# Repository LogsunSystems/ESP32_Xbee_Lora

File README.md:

# Introduction
This is ESP-32 based Wireless Interfacing board which supports Zigbee or LoRa. The board  comes with
either Zigbee or LoRa not both  at a time.

## On-Board Peripherals
The board has sevral On-Board Peripherals like 
	1. LED Bar Graph

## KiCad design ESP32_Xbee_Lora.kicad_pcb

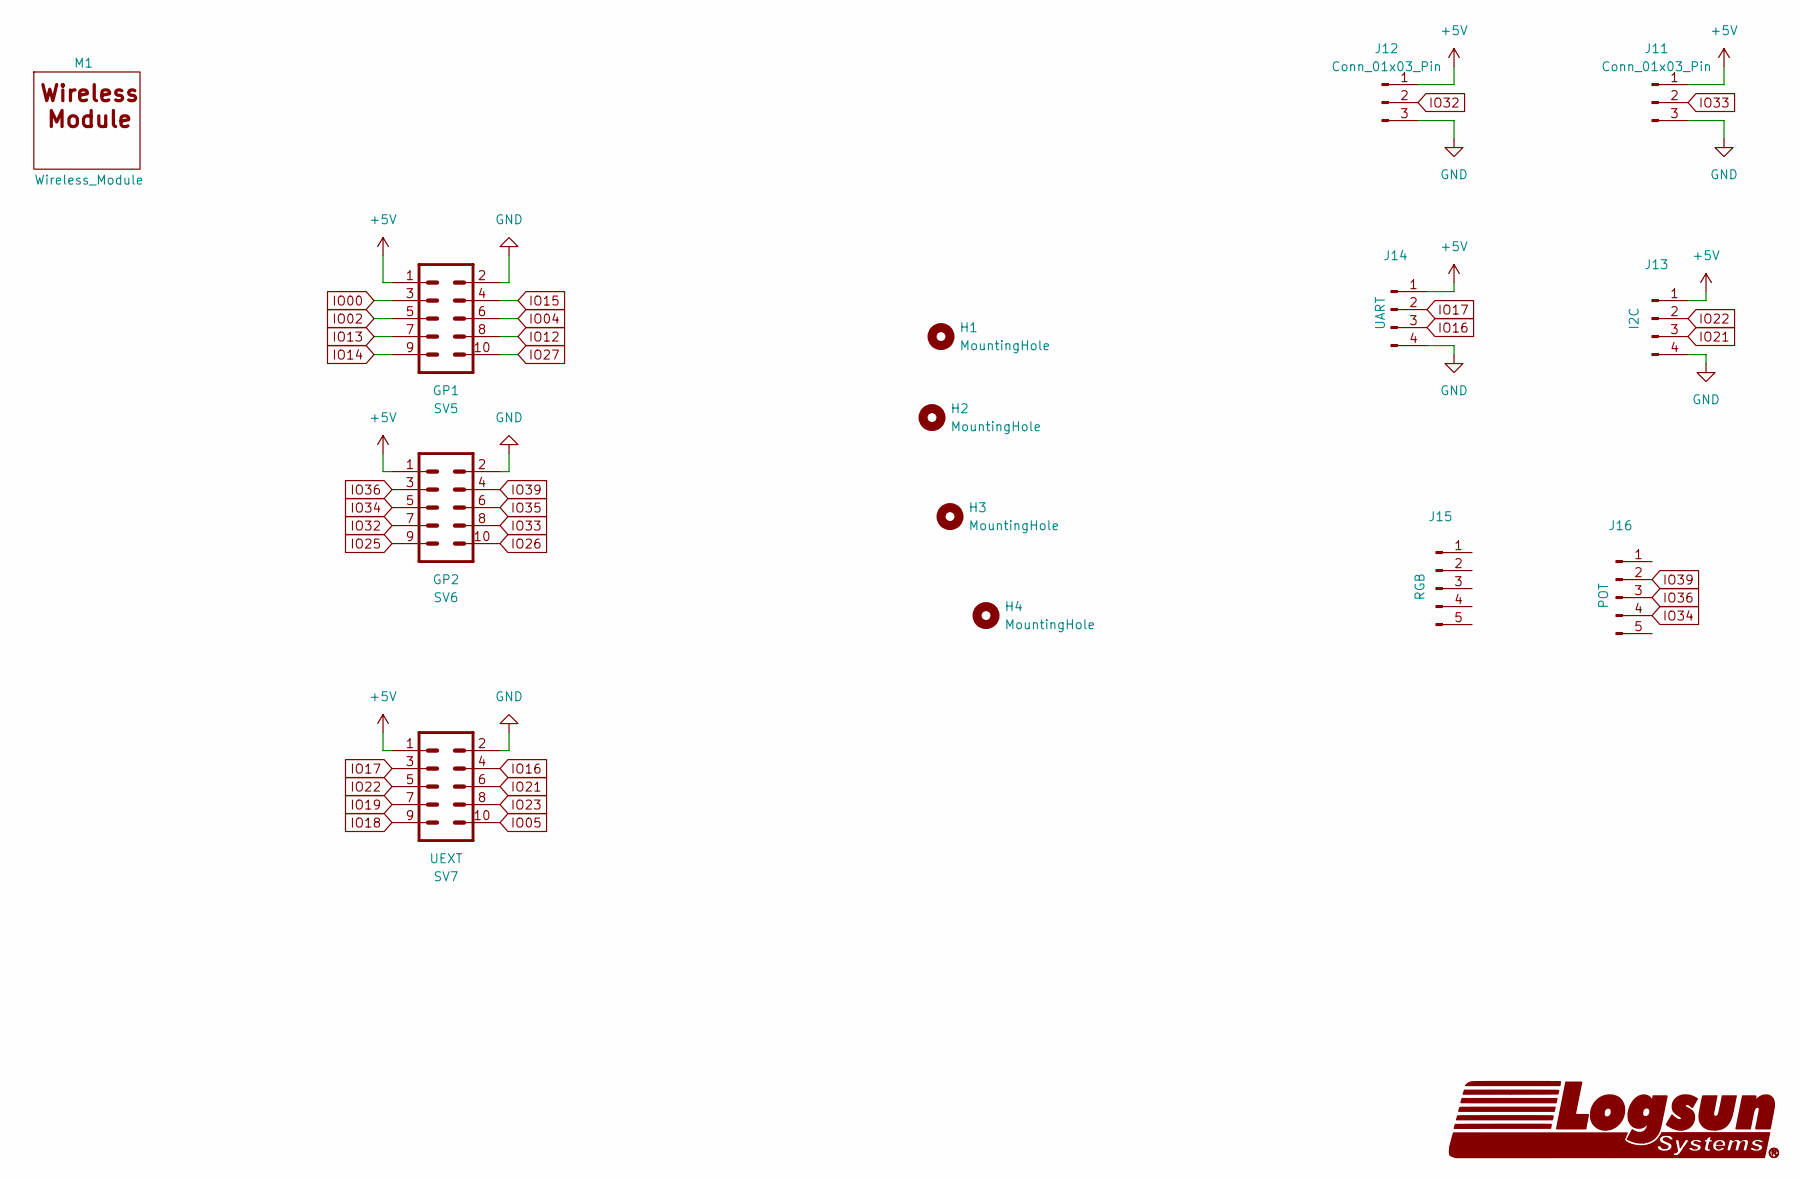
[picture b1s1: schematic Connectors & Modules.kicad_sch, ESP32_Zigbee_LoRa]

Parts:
H1, H2, H3, H4: MountingHole; MountingHole_3.2mm_M3_Pad_Via
J11, J12: Conn_01x03_Pin; JST_EH_B3B-EH-A_1x03_P2.50mm_Vertical
J13: I2C; JST_EH_B4B-EH-A_1x04_P2.50mm_Vertical
J14: UART; JST_EH_B4B-EH-A_1x04_P2.50mm_Vertical
J15: RGB; JST_EH_B5B-EH-A_1x05_P2.50mm_Vertical
J16: POT; JST_EH_B5B-EH-A_1x05_P2.50mm_Vertical
M1: Wireless_Module; LGS-KC-Wireless_Mod
SV5: GP1; LGS-KC-ML10-CONTROLLER
SV6: GP2; LGS-KC-ML10-CONTROLLER
SV7: UEXT; LGS-KC-ML10-CONTROLLER

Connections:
+5V: J11.1, J12.1, J13.1, J14.1, SV5.1, SV6.1, SV7.1; also elsewhere on the board
GND: J11.3, J12.3, J13.4, J14.4, SV5.2, SV6.2, SV7.2; also elsewhere on the board
IO00: SV5.3; also elsewhere on the board
IO02: SV5.5; also elsewhere on the board
IO04: SV5.6; also elsewhere on the board
IO05: SV7.10; also elsewhere on the board
IO12: SV5.8; also elsewhere on the board
IO13: SV5.7; also elsewhere on the board
IO14: SV5.9; also elsewhere on the board
IO15: SV5.4; also elsewhere on the board
IO16: J14.3, SV7.4; also elsewhere on the board
IO17: J14.2, SV7.3; also elsewhere on the board
IO18: SV7.9; also elsewhere on the board
IO19: SV7.7; also elsewhere on the board
IO21: J13.3, SV7.6; also elsewhere on the board
IO22: J13.2, SV7.5; also elsewhere on the board
IO23: SV7.8; also elsewhere on the board
IO25: SV6.9; also elsewhere on the board
IO26: SV6.10; also elsewhere on the board
IO27: SV5.10; also elsewhere on the board
IO32: J12.2, SV6.7; also elsewhere on the board
IO33: J11.2, SV6.8; also elsewhere on the board
IO34: J16.4, SV6.5; also elsewhere on the board
IO35: SV6.6; also elsewhere on the board
IO36: J16.3, SV6.3; also elsewhere on the board
IO39: J16.2, SV6.4; also elsewhere on the board

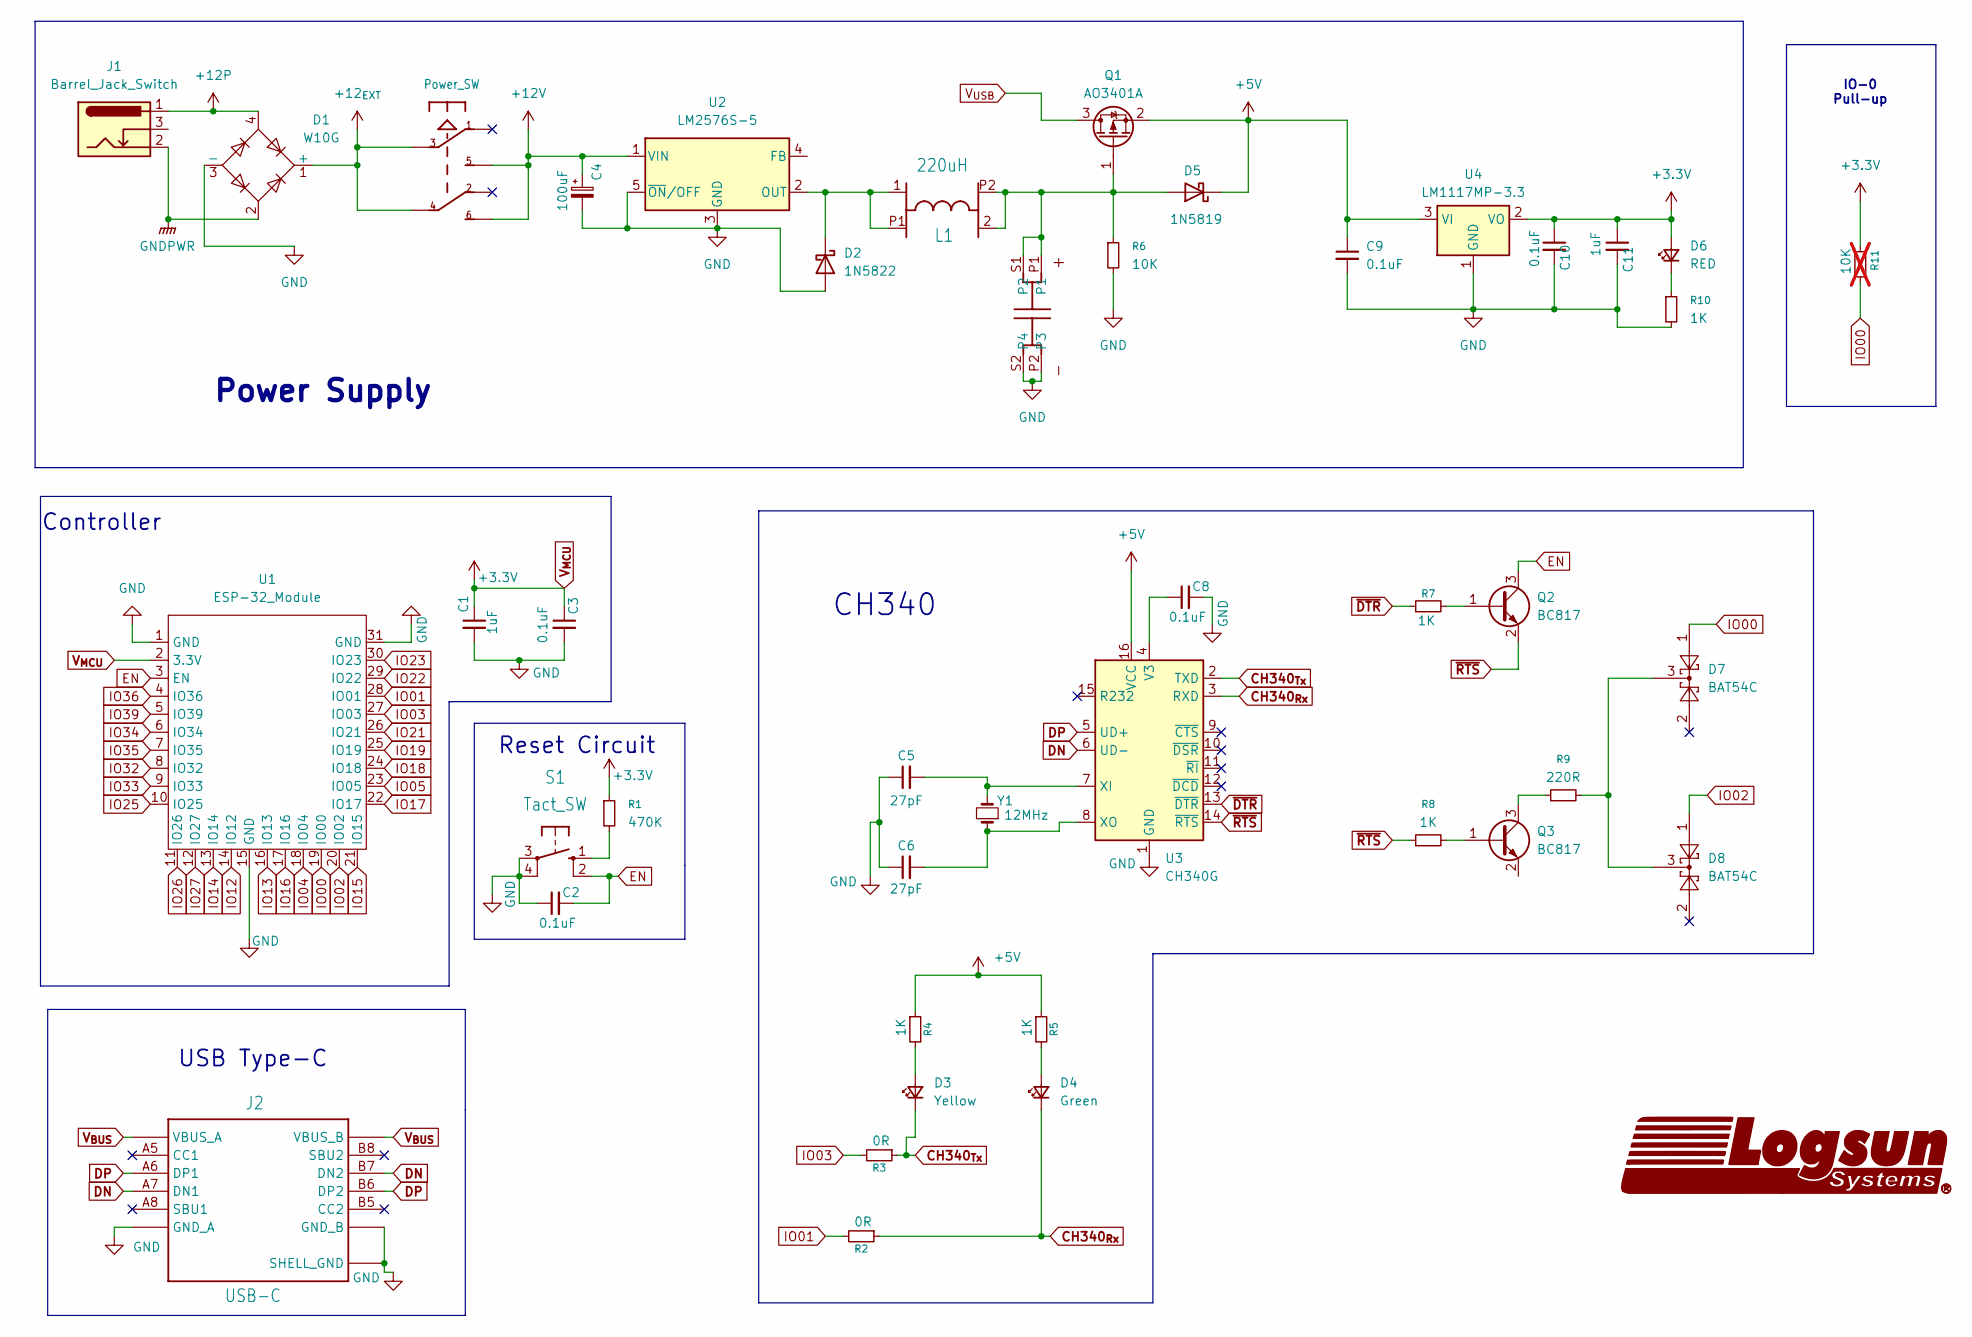
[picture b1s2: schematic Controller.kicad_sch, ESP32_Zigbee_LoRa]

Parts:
C1, C11: 1uF; C_0805_2012Metric_Pad1.18x1.45mm_HandSolder
C2, C3, C8, C9, C10: 0.1uF; C_0805_2012Metric_Pad1.18x1.45mm_HandSolder
C4: 100uF; C_0805_2012Metric_Pad1.18x1.45mm_HandSolder
C5, C6: 27pF; C_0805_2012Metric_Pad1.18x1.45mm_HandSolder
C7: 1000uF; LGS-KC-140CLH-1010
D1: W10G; Diode_Bridge_Round_D9.8mm
D2: 1N5822; D_DO-201AD_P15.24mm_Horizontal
D3: Yellow; LED_1206_3216Metric_ReverseMount_Hole1.8x2.4mm
D4: Green; LED_1206_3216Metric_ReverseMount_Hole1.8x2.4mm
D5: 1N5819; D_DO-41_SOD81_P10.16mm_Horizontal
D6: RED; LED_1206_3216Metric_ReverseMount_Hole1.8x2.4mm
D7, D8: BAT54C; SOT-23
J1: Barrel_Jack_Switch; BarrelJack_Horizontal
J2: USB-C; LGS-KC-VALCON_CSP-USC16-TR
L1: 220uH; LGS-KC-MS42
Q1: AO3401A; SOT-23
Q2, Q3: BC817; SOT-23
R1: 470K; R_0805_2012Metric_Pad1.20x1.40mm_HandSolder
R2, R3: 0R; R_0805_2012Metric_Pad1.20x1.40mm_HandSolder
R4, R5, R7, R8, R10: 1K; R_0805_2012Metric_Pad1.20x1.40mm_HandSolder
R6: 10K; R_0805_2012Metric_Pad1.20x1.40mm_HandSolder
R9: 220R; R_1206_3216Metric_Pad1.30x1.75mm_HandSolder
R11: 10K; R_0805_2012Metric_Pad1.20x1.40mm_HandSolder; not fitted
S1: Tact_SW; LGS-KC-B3F-10XX
SW1: Power_SW; LGS-KC-SLIDE
U1: ESP-32_Module; esp 32 wroom module
U2: LM2576S-5; TO-263-5_TabPin3
U3: CH340G; SOIC-16_3.9x9.9mm_P1.27mm
U4: LM1117MP-3.3; SOT-223-3_TabPin2
Y1: 12MHz; Crystal_HC49-4H_Vertical

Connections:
+5V: C9.1, D5.1 (K), Q1.2 (S), R4.1, R5.1, U3.16 (VCC), U4.3 (VI); also elsewhere on the board
+12P: D1.4, J1.1
+12V: C4.1, SW1.5, SW1.6, U2.1 (VIN)
+12_{EXT}: D1.1 (+), SW1.3, SW1.4
CH340_{Rx}: D4.1 (K), R2.1, U3.3 (RXD)
CH340_{Tx}: D3.1 (K), R3.1, U3.2 (TXD)
DN: J2.A7 (DN1), J2.B7 (DN2), U3.6 (UD-)
DP: J2.A6 (DP1), J2.B6 (DP2), U3.5 (UD+)
EN: C2.2, Q2.3 (C), S1.2 (S1), U1.3 (EN)
GND: C1.2, C2.1, C3.2, C4.2, C5.1, C6.1, C7.P2 (P3), C7.S2 (P4), C8.2, C9.2, C10.2, C11.2, D1.3 (-), D2.2 (A), J2.A1 (GND_A), J2.A12 (GND_A), J2.B1 (GND_B), J2.B12 (GND_B), J2.S1 (SHELL_GND), J2.S2 (SHELL_GND), J2.S3 (SHELL_GND), J2.S4 (SHELL_GND), R6.2, R10.2, S1.3, S1.4 (P1), U1.1 (GND), U1.15 (GND), U1.31 (GND), U2.3 (GND), U2.5 (~ON/OFF), U3.1 (GND), U4.1 (GND); also elsewhere on the board
GNDPWR: D1.2, J1.2
IO00: D7.1, R11.2, U1.19 (IO00); also elsewhere on the board
IO01: R2.2, U1.28 (IO01)
IO02: D8.1, U1.20 (IO02); also elsewhere on the board
IO03: R3.2, U1.27 (IO03)
IO04: U1.18 (IO04); also elsewhere on the board
IO05: U1.23 (IO05); also elsewhere on the board
IO12: U1.14 (IO12); also elsewhere on the board
IO13: U1.16 (IO13); also elsewhere on the board
IO14: U1.13 (IO14); also elsewhere on the board
IO15: U1.21 (IO15); also elsewhere on the board
IO16: U1.17 (IO16); also elsewhere on the board
IO17: U1.22 (IO17); also elsewhere on the board
IO18: U1.24 (IO18); also elsewhere on the board
IO19: U1.25 (IO19); also elsewhere on the board
IO21: U1.26 (IO21); also elsewhere on the board
IO22: U1.29 (IO22); also elsewhere on the board
IO23: U1.30 (IO23); also elsewhere on the board
IO25: U1.10 (IO25); also elsewhere on the board
IO26: U1.11 (IO26); also elsewhere on the board
IO27: U1.12 (IO27); also elsewhere on the board
IO32: U1.8 (IO32); also elsewhere on the board
IO33: U1.9 (IO33); also elsewhere on the board
IO34: U1.6 (IO34); also elsewhere on the board
IO35: U1.7 (IO35); also elsewhere on the board
IO36: U1.4 (IO36); also elsewhere on the board
IO39: U1.5 (IO39); also elsewhere on the board
unnamed: C7.P1, C7.S1 (P2), D5.2 (A), L1.2 (3), L1.P2 (4), Q1.1 (G), R6.1
unnamed: D2.1 (K), L1.1, L1.P1 (2), U2.2 (OUT)
unnamed: D3.2 (A), R4.2
unnamed: D4.2 (A), R5.2
unnamed: D6.1 (K), R10.1
unnamed: D7.3, D8.3, R9.2
unnamed: Q2.1 (B), R7.2
unnamed: Q3.1 (B), R8.2
unnamed: Q3.3 (C), R9.1
unnamed: R1.2, S1.1 (S)
unnamed: C8.1, U3.4 (V3)
unnamed: C5.2, U3.7 (XI), Y1.2
unnamed: C6.2, U3.8 (XO), Y1.1
V_{BUS}: J2.A4 (VBUS_A), J2.A9 (VBUS_A), J2.B4 (VBUS_B), J2.B9 (VBUS_B)
V_{MCU}: C1.1, C3.1, C10.1, C11.1, D6.2 (A), R1.1, R11.1, U1.2 (3.3V), U4.2 (VO)
V_{USB}: Q1.3 (D)
~DTR: R7.1, U3.13 (~DTR)
~RTS: Q2.2 (E), R8.1, U3.14 (~RTS)

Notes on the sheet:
Reset Circuit
Power Supply
Controller
IO-0 Pull-up
USB Type-C
CH340

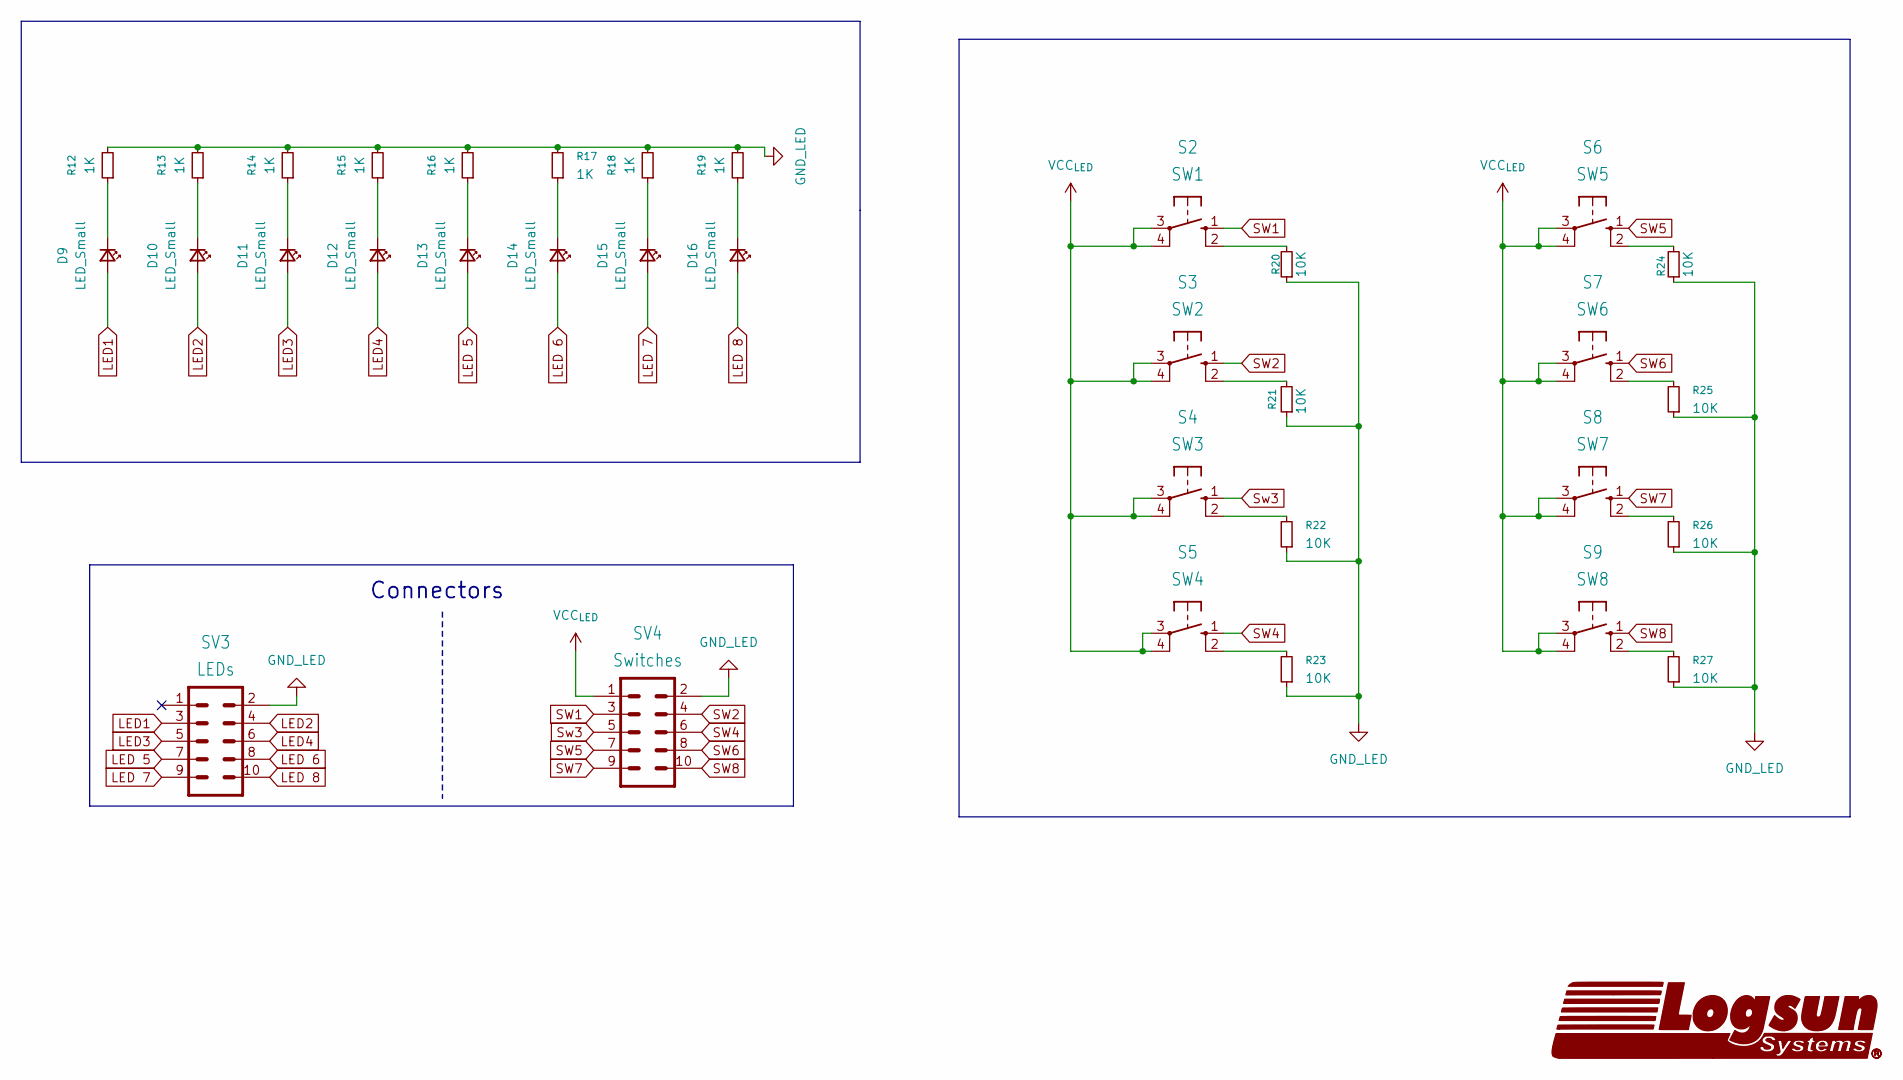
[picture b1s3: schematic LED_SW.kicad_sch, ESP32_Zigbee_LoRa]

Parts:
D9, D10, D11, D12, D13, D14, D15, D16: LED_Small; LED_1206_3216Metric_Pad1.42x1.75mm_HandSolder
R12, R13, R14, R15, R16, R17, R18, R19: 1K; R_0805_2012Metric_Pad1.20x1.40mm_HandSolder
R20, R21, R22, R23, R24, R25, R26, R27: 10K; R_0805_2012Metric_Pad1.20x1.40mm_HandSolder
S2: SW1; LGS-KC-B3F-10XX
S3: SW2; LGS-KC-B3F-10XX
S4: SW3; LGS-KC-B3F-10XX
S5: SW4; LGS-KC-B3F-10XX
S6: SW5; LGS-KC-B3F-10XX
S7: SW6; LGS-KC-B3F-10XX
S8: SW7; LGS-KC-B3F-10XX
S9: SW8; LGS-KC-B3F-10XX
SV3: LEDs; LGS-KC-ML10_INTERFACE
SV4: Switches; LGS-KC-ML10_INTERFACE

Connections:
GND_LED: R12.2, R13.2, R14.2, R15.2, R16.2, R17.2, R18.2, R19.2, R20.1, R21.1, R22.1, R23.1, R24.1, R25.1, R26.1, R27.1, SV3.2, SV4.2
LED1: D9.2 (A), SV3.3
LED2: D10.2 (A), SV3.4
LED3: D11.2 (A), SV3.5
LED4: D12.2 (A), SV3.6
LED 5: D13.2 (A), SV3.7
LED 6: D14.2 (A), SV3.8
LED 7: D15.2 (A), SV3.9
LED 8: D16.2 (A), SV3.10
unnamed: D9.1 (K), R12.1
unnamed: D10.1 (K), R13.1
unnamed: D11.1 (K), R14.1
unnamed: D12.1 (K), R15.1
unnamed: D13.1 (K), R16.1
unnamed: D14.1 (K), R17.1
unnamed: D15.1 (K), R18.1
unnamed: D16.1 (K), R19.1
unnamed: R20.2, S2.2 (S1)
unnamed: R21.2, S3.2 (S1)
unnamed: R22.2, S4.2 (S1)
unnamed: R23.2, S5.2 (S1)
unnamed: R24.2, S6.2 (S1)
unnamed: R25.2, S7.2 (S1)
unnamed: R26.2, S8.2 (S1)
unnamed: R27.2, S9.2 (S1)
SW1: S2.1 (S), SV4.3
SW2: S3.1 (S), SV4.4
SW4: S5.1 (S), SV4.6
SW5: S6.1 (S), SV4.7
SW6: S7.1 (S), SV4.8
SW7: S8.1 (S), SV4.9
SW8: S9.1 (S), SV4.10
Sw3: S4.1 (S), SV4.5
VCC_{LED}: S2.3, S2.4 (P1), S3.3, S3.4 (P1), S4.3, S4.4 (P1), S5.3, S5.4 (P1), S6.3, S6.4 (P1), S7.3, S7.4 (P1), S8.3, S8.4 (P1), S9.3, S9.4 (P1), SV4.1

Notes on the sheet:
Connectors

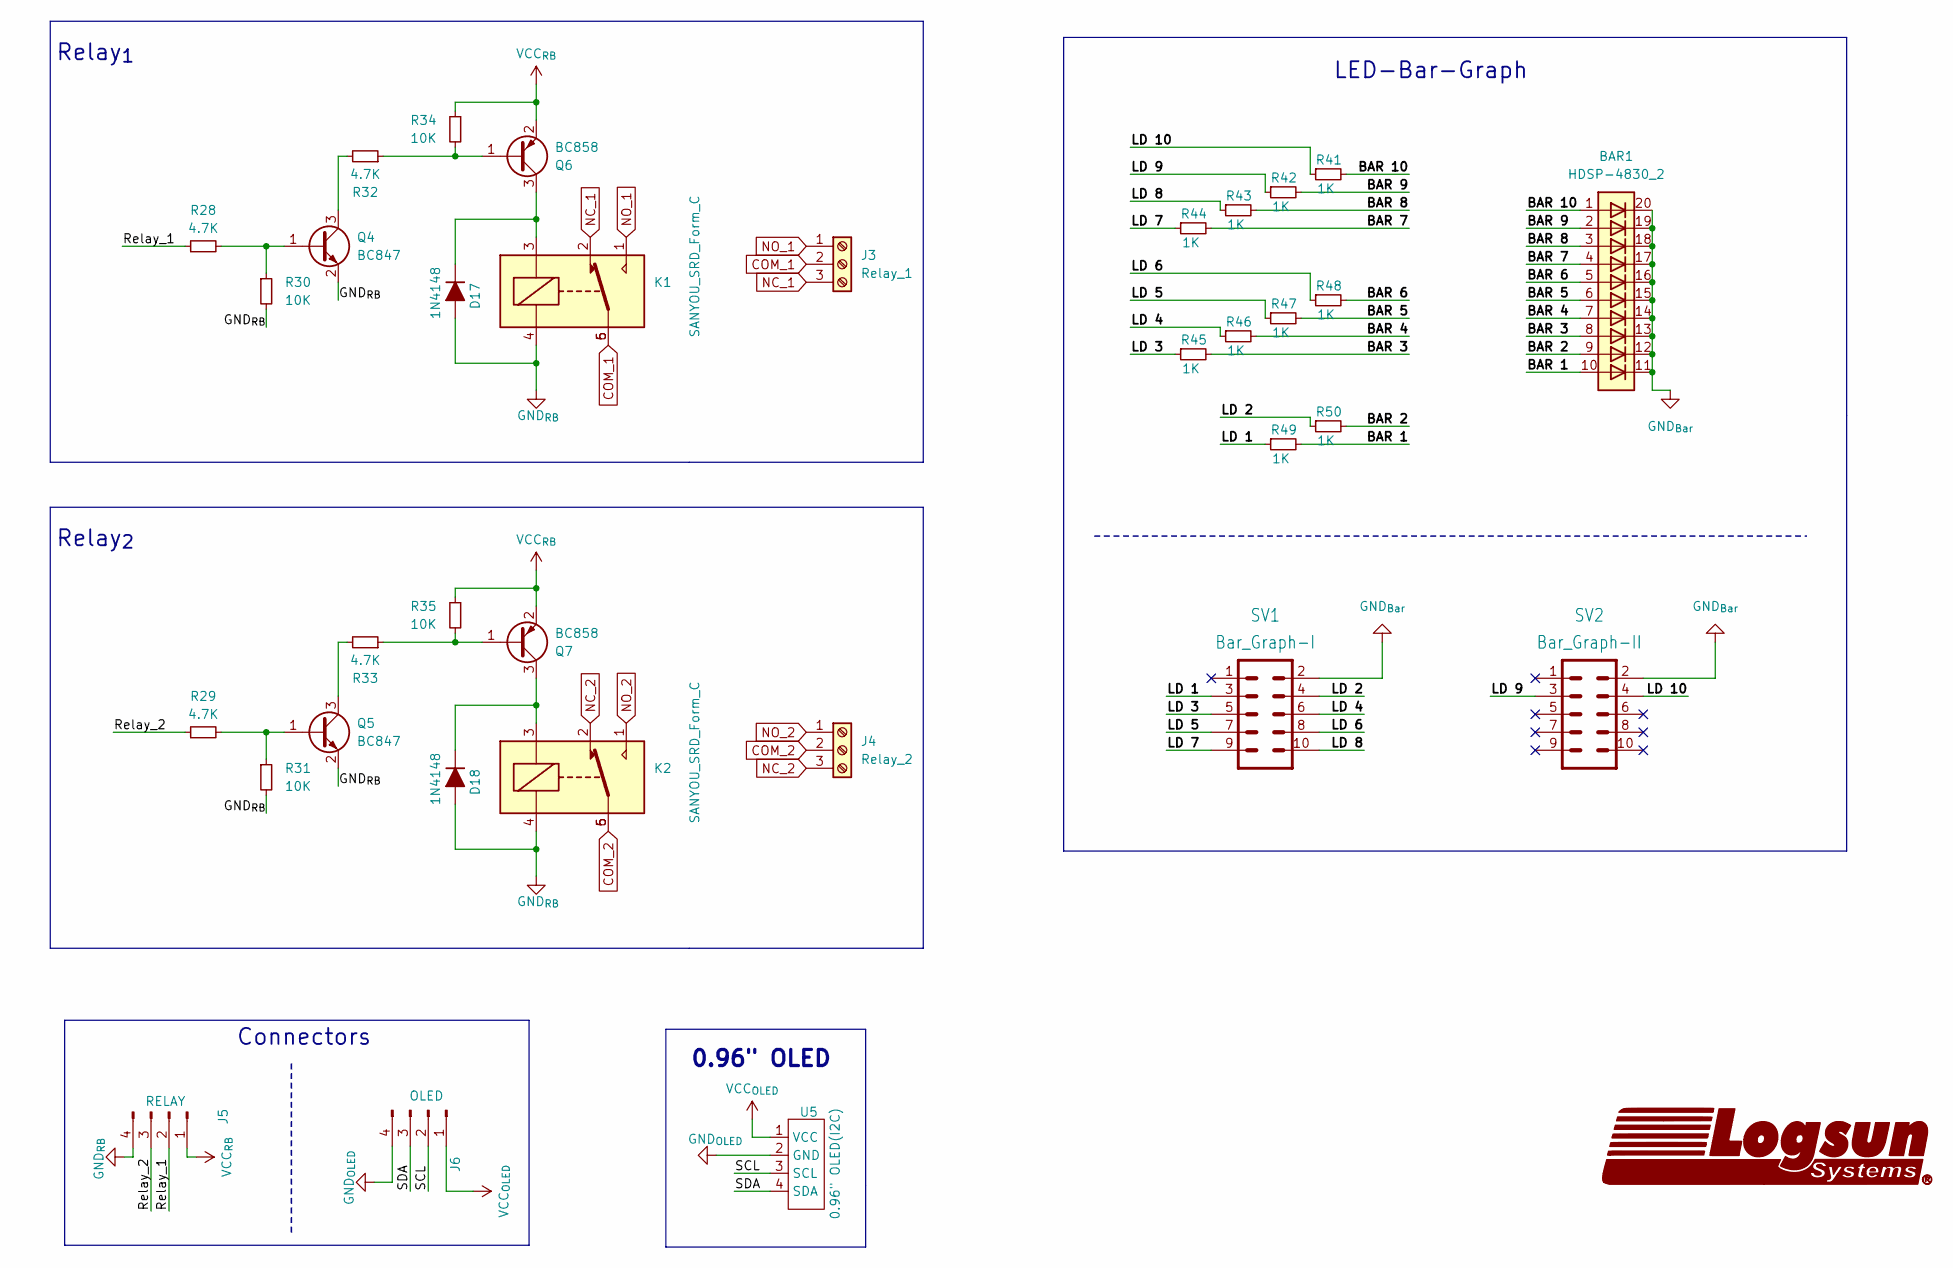
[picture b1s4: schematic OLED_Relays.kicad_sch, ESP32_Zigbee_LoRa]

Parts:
BAR1: HDSP-4830_2; HDSP-4830
D17, D18: 1N4148; D_DO-35_SOD27_P7.62mm_Horizontal
J3: Relay_1; TerminalBlock_Phoenix_MKDS-1,5-3-5.08_1x03_P5.08mm_Horizont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
J4: Relay_2; TerminalBlock_Phoenix_MKDS-1,5-3-5.08_1x03_P5.08mm_Horizont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
J5: RELAY; JST_EH_B4B-EH-A_1x04_P2.50mm_Vertical
J6: OLED; JST_EH_B4B-EH-A_1x04_P2.50mm_Vertical
K1, K2: SANYOU_SRD_Form_C; LGS-KC-FRS1B
Q4, Q5: BC847; SOT-23
Q6, Q7: BC858; SOT-23
R28, R29, R32, R33: 4.7K; R_0805_2012Metric_Pad1.20x1.40mm_HandSolder
R30, R31, R34, R35: 10K; R_0805_2012Metric_Pad1.20x1.40mm_HandSolder
R41, R42, R43, R44, R45, R46, R47, R48, R49, R50: 1K; R_0805_2012Metric_Pad1.20x1.40mm_HandSolder
SV1: Bar_Graph-I; LGS-KC-ML10_INTERFACE
SV2: Bar_Graph-II; LGS-KC-ML10_INTERFACE
U5: 0.96" OLED(I2C); OLED I2C

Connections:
/OLED_Relays/BAR 1: BAR1.10 (A), R49.2
/OLED_Relays/BAR 2: BAR1.9 (A), R50.2
/OLED_Relays/BAR 3: BAR1.8 (A), R45.2
/OLED_Relays/BAR 4: BAR1.7 (A), R46.2
/OLED_Relays/BAR 5: BAR1.6 (A), R47.2
/OLED_Relays/BAR 6: BAR1.5 (A), R48.2
/OLED_Relays/BAR 7: BAR1.4 (A), R44.2
/OLED_Relays/BAR 8: BAR1.3 (A), R43.2
/OLED_Relays/BAR 9: BAR1.2 (A), R42.2
/OLED_Relays/BAR 10: BAR1.1 (A), R41.2
/OLED_Relays/LD 1: R49.1, SV1.3
/OLED_Relays/LD 2: R50.1, SV1.4
/OLED_Relays/LD 3: R45.1, SV1.5
/OLED_Relays/LD 4: R46.1, SV1.6
/OLED_Relays/LD 5: R47.1, SV1.7
/OLED_Relays/LD 6: R48.1, SV1.8
/OLED_Relays/LD 7: R44.1, SV1.9
/OLED_Relays/LD 8: R43.1, SV1.10
/OLED_Relays/LD 9: R42.1, SV2.3
/OLED_Relays/LD 10: R41.1, SV2.4
/OLED_Relays/Relay_1: J5.2, R28.1
/OLED_Relays/Relay_2: J5.3, R29.1
/OLED_Relays/SCL: J6.2, U5.3 (SCL)
/OLED_Relays/SDA: J6.3, U5.4 (SDA)
COM_1: J3.2, K1.5, K1.6
COM_2: J4.2, K2.5, K2.6
GND_{Bar}: BAR1.11 (K), BAR1.12 (K), BAR1.13 (K), BAR1.14 (K), BAR1.15 (K), BAR1.16 (K), BAR1.17 (K), BAR1.18 (K), BAR1.19 (K), BAR1.20 (K), SV1.2, SV2.2
GND_{OLED}: J6.4, U5.2 (GND)
GND_{RB}: D17.2 (A), D18.2 (A), J5.4, K1.4, K2.4, Q4.2 (E), Q5.2 (E), R30.2, R31.2
NC_1: J3.3, K1.2
NC_2: J4.3, K2.2
NO_1: J3.1, K1.1
NO_2: J4.1, K2.1
unnamed: D17.1 (K), K1.3, Q6.3 (C)
unnamed: D18.1 (K), K2.3, Q7.3 (C)
unnamed: Q4.1 (B), R28.2, R30.1
unnamed: Q4.3 (C), R32.2
unnamed: Q5.1 (B), R29.2, R31.1
unnamed: Q5.3 (C), R33.2
unnamed: Q6.1 (B), R32.1, R34.2
unnamed: Q7.1 (B), R33.1, R35.2
VCC_{OLED}: J6.1, U5.1 (VCC)
VCC_{RB}: J5.1, Q6.2 (E), Q7.2 (E), R34.1, R35.1

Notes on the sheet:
0.96" OLED
LED-Bar-Graph
Relay_{2}
Relay_{1}
Connectors

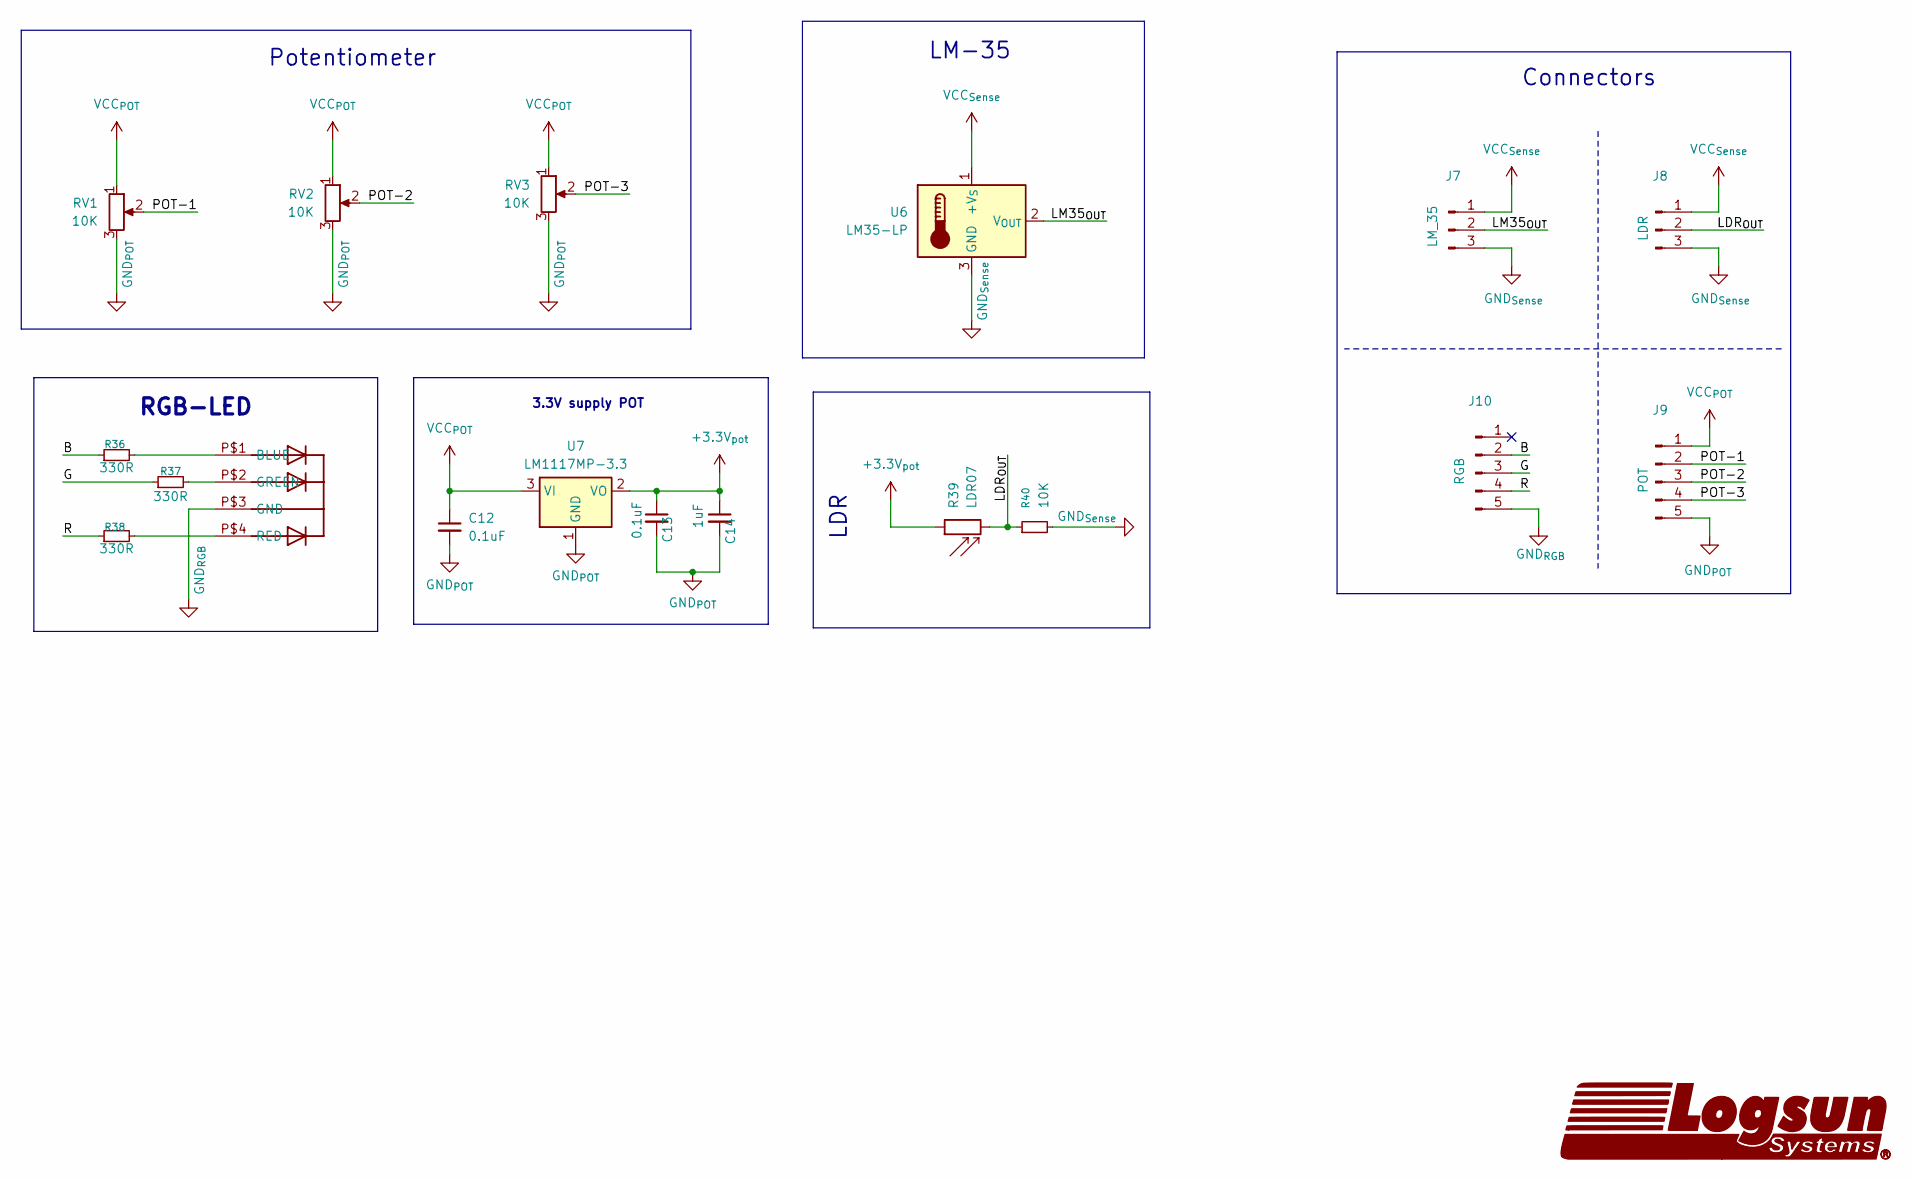
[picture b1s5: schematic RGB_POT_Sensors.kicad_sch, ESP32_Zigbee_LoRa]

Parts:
C12, C13: 0.1uF; C_0805_2012Metric_Pad1.18x1.45mm_HandSolder
C14: 1uF; C_0805_2012Metric_Pad1.18x1.45mm_HandSolder
D19: LGS-KC-LED5MMRGB
J7: LM_35; JST_EH_B3B-EH-A_1x03_P2.50mm_Vertical
J8: LDR; JST_EH_B3B-EH-A_1x03_P2.50mm_Vertical
J9: POT; JST_EH_B5B-EH-A_1x05_P2.50mm_Vertical
J10: RGB; JST_EH_B5B-EH-A_1x05_P2.50mm_Vertical
R36, R37, R38: 330R; R_0805_2012Metric_Pad1.20x1.40mm_HandSolder
R39: LDR07; R_LDR_5.1x4.3mm_P3.4mm_Vertical
R40: 10K; R_0805_2012Metric_Pad1.20x1.40mm_HandSolder
RV1, RV2, RV3: 10K; LGS-KC-CA6V
U6: LM35-LP; TO-92_Inline
U7: LM1117MP-3.3; SOT-223-3_TabPin2

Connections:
+3.3V_{pot}: C13.1, C14.1, R39.1, U7.2 (VO)
/RGB_POT_Sensors/B: J10.2, R36.1
/RGB_POT_Sensors/G: J10.3, R37.1
/RGB_POT_Sensors/LDR_{OUT}: J8.2, R39.2, R40.1
/RGB_POT_Sensors/LM35_{OUT}: J7.2, U6.2 (V_{OUT})
/RGB_POT_Sensors/POT-1: J9.2, RV1.2
/RGB_POT_Sensors/POT-2: J9.3, RV2.2
/RGB_POT_Sensors/POT-3: J9.4, RV3.2
/RGB_POT_Sensors/R: J10.4, R38.1
GND_{POT}: C12.2, C13.2, C14.2, J9.5, RV1.3, RV2.3, RV3.3, U7.1 (GND)
GND_{RGB}: D19.P$3 (GND), J10.5
GND_{Sense}: J7.3, J8.3, R40.2, U6.3 (GND)
unnamed: D19.P$1 (BLUE), R36.2
unnamed: D19.P$2 (GREEN), R37.2
unnamed: D19.P$4 (RED), R38.2
VCC_{POT}: C12.1, J9.1, RV1.1, RV2.1, RV3.1, U7.3 (VI)
VCC_{Sense}: J7.1, J8.1, U6.1 (+V_{S})

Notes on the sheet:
Connectors
RGB-LED
Potentiometer
LDR
3.3V supply POT
LM-35

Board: 2 copper layers, 143 parts (5 on the bottom side), 144 nets, no tracks yet.

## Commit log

2026-03-16 PCB Netclass and Constrained Set
2026-03-16 Temporary files omiited from staging
2026-03-16 Power Supply Schematic Completed
2026-03-16 Autosave files
2026-03-16 Controller Section Schematic Done
2026-03-16 Backup files added
2026-03-16 LED Switch secton done and schematic files added for other sections
2026-03-16 Footprint cache added
2026-03-16 Backup managed
2026-03-16 OLED, Relay and Bar graph added
2026-03-16 Backups added
2026-03-16 AUtosave
2026-03-17 RGB,POT and sensors added
2026-03-17 Connectors Added
2026-03-17 Footprint cache updated
2026-03-17 Schematic Completed, Footprints Assigned
2026-03-17 Backups updated
2026-03-24 Bar LED Resistors Added & Mounting holes added
2026-03-24 Tentative Placement Done
2026-03-24 Symbol and footprint library exported
